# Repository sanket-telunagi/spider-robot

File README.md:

# Spyder Robot

The Spyder Robot is a four-legged Quadruped robot featuring synchronized leg control through servo motors. It incorporates 3D printed design parts for enhanced functionality and mobility.

## Key Features

- **Quadruped Design:** Four-legged robot for stability and maneuverability.
- **Synchronized Leg Control:** Precise leg movement achieved through synchronized servo motor control.
- **3D Printed Components:** Integration of 3D printed parts to optimize functionality and design.
- **Control System:** Engineered with an Atmega-8a microcontroller and a custom PCB with SMD components.
  
## Components Used

- **Atmega 8A Microcontroller:** Central control unit for the robot's functionalities.
- **Servo Motors:** Used for precise leg movement and control.
- **KiCAD:** Utilized for the schematic design and layout of the custom PCB.
- **Arduino IDE:** Programming environment used for coding the Atmega microcontroller.
- **SMD Components:** Integrated into the custom PCB for circuitry and functionality.

## Functionality

The Spyder Robot's capabilities include:

- **Stable Mobility:** Designed for stability and agility in various terrains.
- **Precise Leg Control:** Enables precise movement and coordination of leg motions.
- **Customizable Design:** Modular components allow for easy customization and upgrades.

## Tools & Development

- **KiCAD:** Used for designing the custom PCB layout.
- **Arduino IDE:** Programming and code development for the Atmega-8a microcontroller.

## Credits

- This project was possible because of my teammates and guidance from teachers 
- Teammates are : 
    - Yash Mali 
    - Vaibhav Nanne 

## License

The-Spider-Robot © 2023 by Sanket Telunagi is licensed under CC BY 4.0

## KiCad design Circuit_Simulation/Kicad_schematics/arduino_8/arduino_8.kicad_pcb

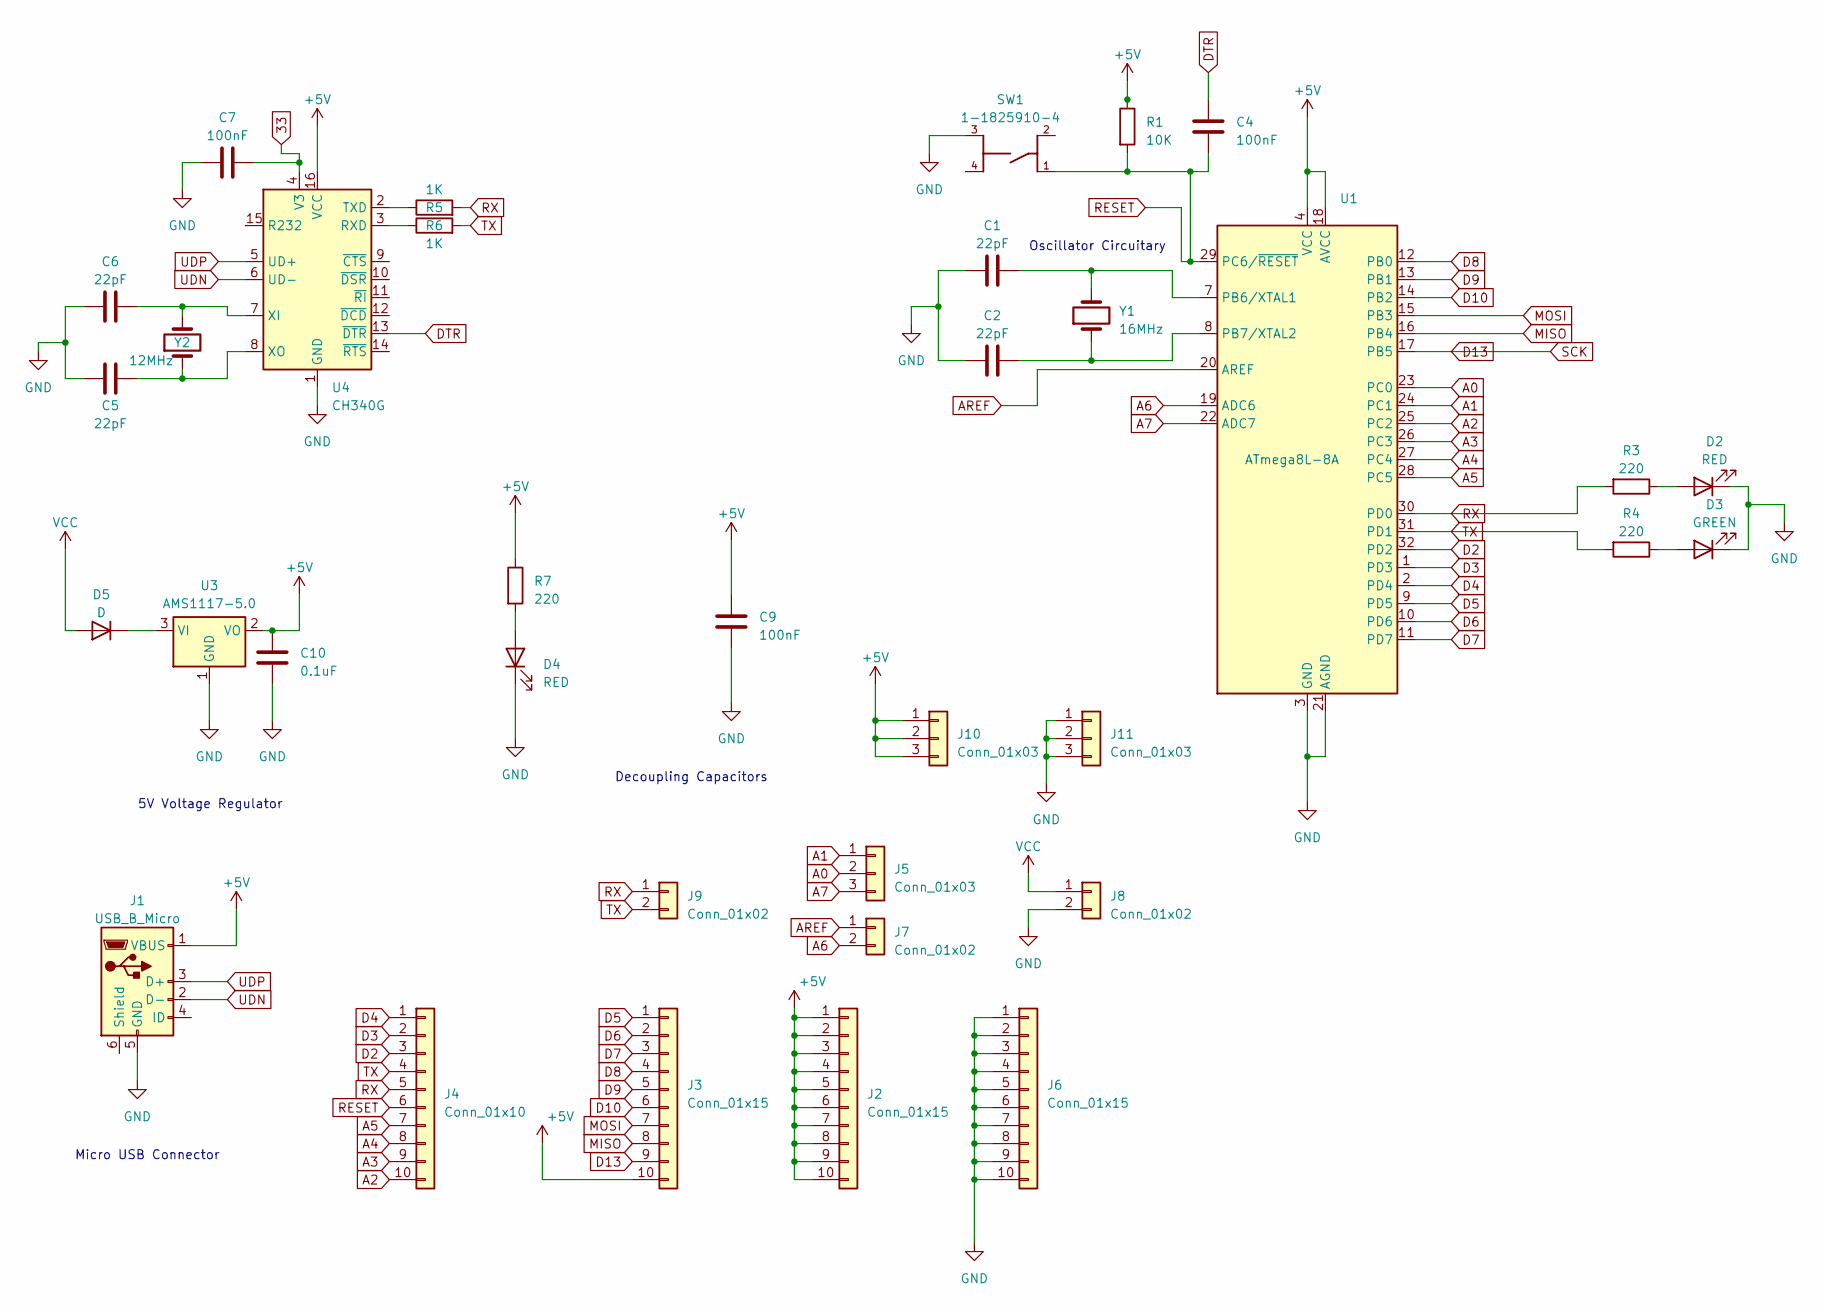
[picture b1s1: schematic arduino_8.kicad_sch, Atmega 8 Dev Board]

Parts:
C1, C2, C5, C6: 22pF; C_0805_2012Metric_Pad1.18x1.45mm_HandSolder
C4, C7, C9: 100nF; C_0805_2012Metric_Pad1.18x1.45mm_HandSolder
C10: 0.1uF; C_0805_2012Metric_Pad1.18x1.45mm_HandSolder
D2, D4: RED; LED_0805_2012Metric_Pad1.15x1.40mm_HandSolder
D3: GREEN; LED_0805_2012Metric_Pad1.15x1.40mm_HandSolder
D5: D; D_1206_3216Metric_Pad1.42x1.75mm_HandSolder
J1: USB_B_Micro; USB_Micro-B_Amphenol_10104110_Horizontal
J2, J3, J6: Conn_01x15; PinHeader_1x10_P2.54mm_Vertical
J4: Conn_01x10; PinHeader_1x10_P2.54mm_Vertical
J5, J10, J11: Conn_01x03; PinHeader_1x03_P2.54mm_Vertical
J7, J8, J9: Conn_01x02; PinHeader_1x02_P2.54mm_Vertical
R1: 10K; R_0805_2012Metric_Pad1.20x1.40mm_HandSolder
R3, R4, R7: 220; R_0805_2012Metric_Pad1.20x1.40mm_HandSolder
R5, R6: 1K; R_0805_2012Metric_Pad1.20x1.40mm_HandSolder
SW1: 1-1825910-4; TE_1-1825910-4; PARTREV C10
U1: ATmega8L-8A; TQFP-32_7x7mm_P0.8mm
U3: AMS1117-5.0; SOT-223-3_TabPin2
U4: CH340G; SOIC-16_3.9x9.9mm_P1.27mm
Y1: 16MHz; Crystal_HC49-U_Vertical
Y2: 12MHz; Crystal_HC49-U_Vertical

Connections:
33: C7.2, U4.4 (V3)
+5V: C9.1, C10.1, J1.1 (VBUS), J2.1, J2.2, J2.3, J2.4, J2.5, J2.6, J2.7, J2.8, J2.9, J2.10, J3.10, J10.1, J10.2, J10.3, R1.1, R7.1, U1.4 (VCC), U1.6 (VCC), U1.18 (AVCC), U3.2 (VO), U4.16 (VCC)
A0: J5.2, U1.23 (PC0)
A1: J5.1, U1.24 (PC1)
A2: J4.10, U1.25 (PC2)
A3: J4.9, U1.26 (PC3)
A4: J4.8, U1.27 (PC4)
A5: J4.7, U1.28 (PC5)
A6: J7.2, U1.19 (ADC6)
A7: J5.3, U1.22 (ADC7)
AREF: J7.1, U1.20 (AREF)
D2: J4.3, U1.32 (PD2)
D3: J4.2, U1.1 (PD3)
D4: J4.1, U1.2 (PD4)
D5: J3.1, U1.9 (PD5)
D6: J3.2, U1.10 (PD6)
D7: J3.3, U1.11 (PD7)
D8: J3.4, U1.12 (PB0)
D9: J3.5, U1.13 (PB1)
D10: J3.6, U1.14 (PB2)
D13: J3.9, U1.17 (PB5)
DTR: C4.1, U4.13 (~DTR)
GND: C1.1, C2.1, C5.1, C6.2, C7.1, C9.2, C10.2, D2.1 (K), D3.1 (K), D4.1 (K), J1.5 (GND), J6.1, J6.2, J6.3, J6.4, J6.5, J6.6, J6.7, J6.8, J6.9, J6.10, J8.2, J11.1, J11.2, J11.3, SW1.3, U1.3 (GND), U1.5 (GND), U1.21 (AGND), U3.1 (GND), U4.1 (GND)
MISO: J3.8, U1.16 (PB4)
MOSI: J3.7, U1.15 (PB3)
unnamed: D2.2 (A), R3.1
unnamed: D3.2 (A), R4.1
unnamed: D4.2 (A), R7.2
unnamed: D5.1 (K), U3.3 (VI)
unnamed: C1.2, U1.7 (PB6/XTAL1), Y1.2
unnamed: C2.2, U1.8 (PB7/XTAL2), Y1.1
unnamed: R6.1, U4.3 (RXD)
unnamed: R5.1, U4.2 (TXD)
unnamed: C6.1, U4.7 (XI), Y2.2
unnamed: C5.2, U4.8 (XO), Y2.1
RESET: C4.2, J4.6, R1.2, SW1.1, U1.29 (PC6/~RESET)
RX: J4.5, J9.1, R3.2, R5.2, U1.30 (PD0)
TX: J4.4, J9.2, R4.2, R6.2, U1.31 (PD1)
UDN: J1.2 (D-), U4.6 (UD-)
UDP: J1.3 (D+), U4.5 (UD+)
VCC: D5.2 (A), J8.1

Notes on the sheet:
Oscillator Circuitary
5V Voltage Regulator
Micro USB Connector
Decoupling Capacitors

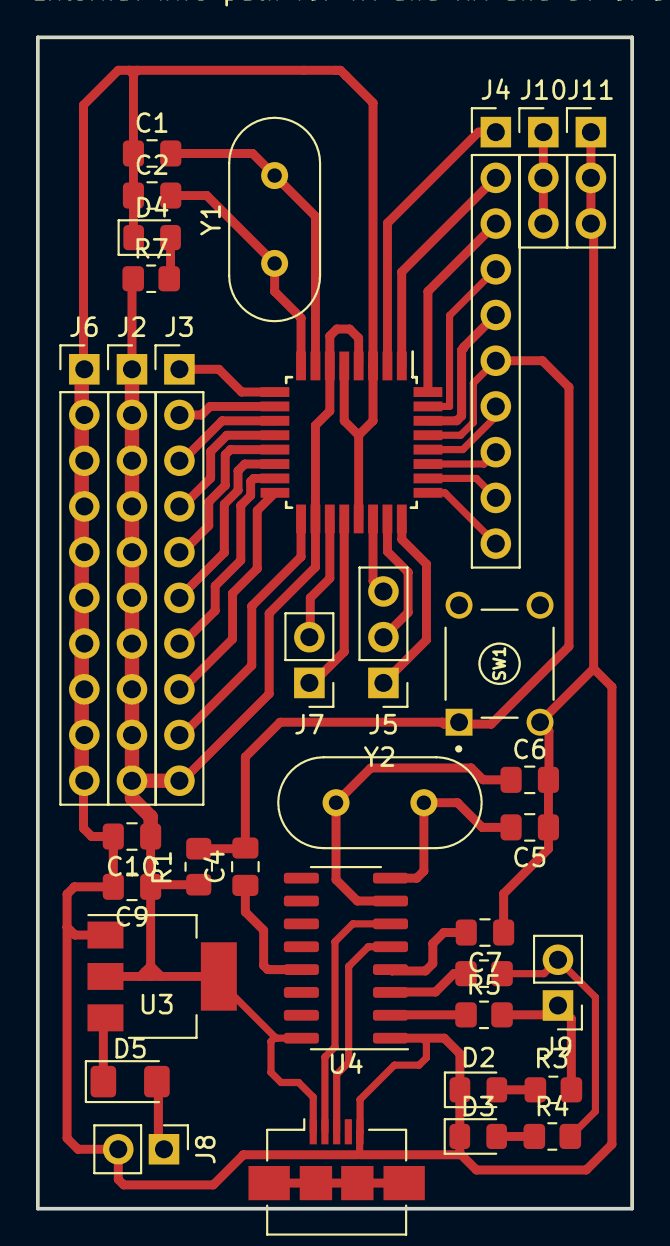
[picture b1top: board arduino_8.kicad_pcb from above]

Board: 2 copper layers, 33.0 x 65.1 mm, 35 parts (0 on the bottom side), 41 nets.

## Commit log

2023-11-17 complete project
